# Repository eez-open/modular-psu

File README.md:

### Ownership and License
The contributors are listed in CONTRIB.TXT. 

Licenses | OSHWA UID
--|--
 | 

### Introduction

EEZ Bench Box 3 (BB3) represents a new category of *modular* Test and Measurement (T&M) equipment. It provides a complete open-source hardware and software framework that bridges the gap between – and combines the best features of – DIY hobbyist tools and professional benchtop equipment. 
BB3 was inspired by the [EEZ H24005](https://github.com/eez-open/psu-hw) power supply project ([OSHWA UID HR000001](https://certification.oshwa.org/hr000001.html)), which attracted many enthusiasts with its broad feature-set, rich user interface, DIY-friendliness, and fully open-source design. 
It initially comes with two DC power modules (hence the name of repository *modular-psu*) and will be expanded with new T&M modules (e.g. multi-channel power source, 2/4-quadrant power module, multi-channel temperature sensor module, data logger, switch matrix, digital I/O expander, function generator, data acquisition module, etc.). 
BB3 is made up of the following components:

* _[BP3C](https://github.com/eez-open/modular-psu/tree/master/bp3c)_ EEZ DIB backplane with power output coupling capability of first two modules
* _[AUX power supply](https://github.com/eez-open/modular-psu/tree/master/aux-ps)_ board with AC input protection, soft-start/power-up control, DC fan controller and +5 V / +12 V power outputs
* _[MCU](https://github.com/eez-open/modular-psu/tree/master/mcu)_ board based on STM32F769IIT6 32-bit ARM Cortex-M7
* _[DCP405](https://github.com/eez-open/modular-psu/tree/master/dcp405)_, 0 - 40 V / 50 mA / 5 A DC power source module
* _[DCM224](https://github.com/eez-open/dib-dcm224)_, dual sync buck 1 - 24 V / max. 4.9 A module (**retired**)
* _[Metal enclosure](https://github.com/eez-open/modular-psu/tree/master/enclosure)_ for housing up to 3 modules with 4.3" TFT LCD. Dimensions: 290 (W) x 123 (H) x 240 (D) mm

### Supported technologies

* _EEZ Flow_ (Visual programming tool for test and measurement automation)
* SCPI (Reference Guide in [PDF](https://github.com/eez-open/modular-psu-firmware/blob/master/docs/SCPI%20reference%20guide/EEZ%20BB3%20SCPI%20reference%20guide.pdf))
* MicroPython (script [examples](https://github.com/eez-open/modular-psu-firmware/tree/master/scripts), an example [video](https://www.youtube.com/watch?v=I0y6fgv8G00))
* MQTT (an intro [video](https://www.youtube.com/watch?v=THyfLSSAhrI))
* Node-RED integration (an intro [video](https://www.youtube.com/watch?v=0xQ6Xuq53fA))

### Other DIB modules

* [MIO168](https://github.com/eez-open/dib-mio168) Mixed I/O module
* [PREL6](https://github.com/eez-open/dib-prel6) power relays module
* [SMX46](https://github.com/eez-open/dib-smx46) programmable switch matrix module
* [MUX14D](https://github.com/eez-open/dib-mux14d) dual 7:1 reed relay 2-wire multiplexer

### Related topics and links

* EEZ BB3 [firmware](https://github.com/eez-open/modular-psu-firmware)
* [EEZ Studio](https://www.envox.eu/studio/studio-introduction)
* EEZ [DIB v1.2](https://github.com/eez-open/modular-psu/tree/master/DIB) specification
* EEZ DIB peripheral modules [KiCad 8.x project template](https://github.com/eez-open/dib-kicad-template)
* [Discord](https://discord.gg/dhYMnCB) server
* [X](https://x.com/envox) (ex Twitter)
* [YouTube](https://www.youtube.com/c/eezopen) channel
* [EEVblog forum](https://www.eevblog.com/forum/projects/eez-h25005-a-possible-successor-of-eez-h24005-programmable-power-supply/) discussion
* [Crowd Supply](https://www.crowdsupply.com/envox/eez-bb3) crowdfunding landing page
* [EMC certificate](https://www.envox.eu/?smd_process_download=1&download_id=2806), [LVD cerificate](https://www.envox.eu/?smd_process_download=1&download_id=2808)
* [Sigrok](https://sigrok.org/wiki/Envox_EEZ_Bench_Box_3)
* [Liberpay](https://liberapay.com/eez-open/donate) donations 

### Where to buy?

* [EEZ Web store](https://www.envox.eu/store) (out of stock)
* [Mouser](https://www.mouser.com/Search/Refine?Keyword=cs-bb3-) (kit only, excl. EU/UK)
* [Crowd supply](https://www.crowdsupply.com/envox/eez-bb3) (kit only, excl. EU/UK)

### Security & Regulatory Compliance

* [CRA Compliance Documentation](./security/README.md)

---
Please note that some previous board types and revisions that could be still usable in some cases can be found under *[previous design](https://github.com/eez-open/modular-psu/tree/master/previous%20designs)* folder.

### Notes on Shell Syntax (Community Feedback)
In shell scripting, the syntax used for loops can impact portability and readability across different environments.
Potential Issue with Braces:

 while (( i++ < 10 )) { echo i is $i } 
 
may not work reliably in all shell environments. For instance, in Zsh, this syntax will fail unless SHORT_LOOPS is explicitly enabled.
It can also cause issues with syntax highlighting and script execution.

* Alternate Approach: To ensure broader compatibility and clearer syntax, prefer the standard do ... done block structure:

i=0
while (( i++ < 10 ))
do
 echo "i is $i"
done

This format is - Compatible with most POSIX-compliant shells (e.g., Bash, Zsh, etc.) and Syntax-highlight friendly in editors and IDEs.

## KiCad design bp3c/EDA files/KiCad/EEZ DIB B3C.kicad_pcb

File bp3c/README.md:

EEZ DIB BP3C is backplane for connecting up to three EEZ DIB peripheral modules. When power modules (e.g. [DCP405](https://github.com/eez-open/modular-psu/tree/master/dcp405)) are plugged into slot #1 and #2, their outputs can be combined under firmware control in one of the following way:

- Serial coupling to double max. output voltage 
- Parallel coupling to double max. output current
- Ch#1 `Out-` and Ch#2 `Out+` coupling for split rail output

Additionaly, it is possible to couple `Out-` terminals of all installed power modules (common GND).

The BP3C backplane provides dedicated BOOT output for each peripheral module that comes with on-board MCU and which firmware could be uploaded via SPI or UART. Programmable reset output is also featured that firmware upload procedure can be initiated without power recycling.

Dimensions: 110 x 90 mm, 2-layer PCB

### KiCad project (v7 or newer)

* [BP3C r3B3](https://github.com/eez-open/modular-psu/tree/master/bp3c/EDA%20files/KiCad)

All symbols, footprints and 3D models used in the project can be found in the [EEZ-DIB Library](https://github.com/eez-open/eez-kicad-libraries) plugin for KiCad.

### Bill of materials

* [Download](https://github.com/eez-open/modular-psu/blob/master/bp3c/EDA%20files/KiCad/bom/ibom.html) as raw file _Interactive BOM_ (ibom.html) and open it locally in your browser.

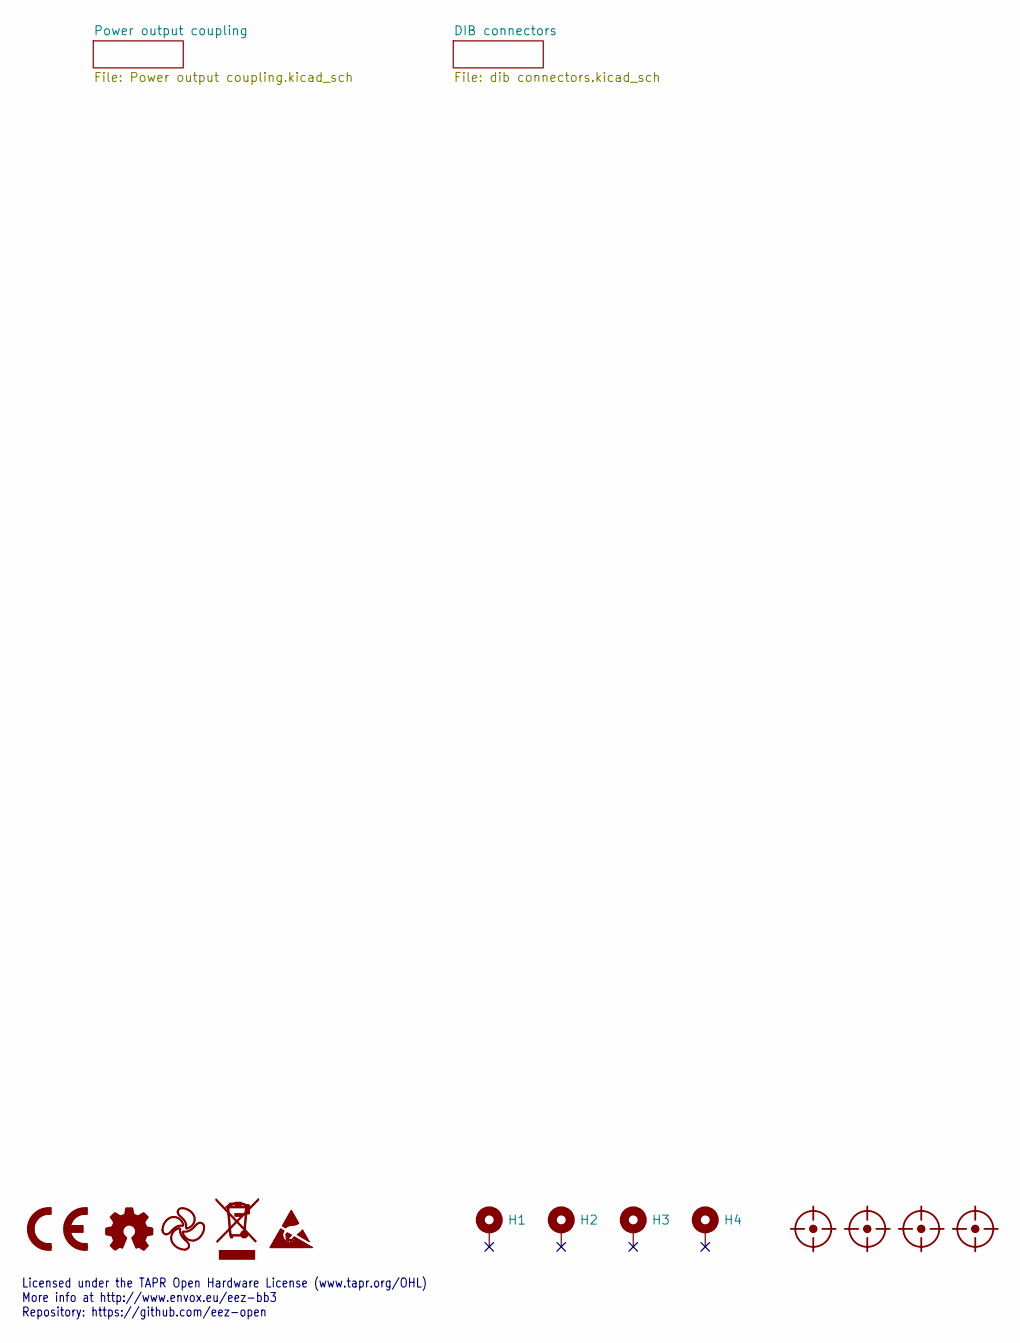
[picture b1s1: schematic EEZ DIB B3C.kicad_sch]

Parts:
FM1, FM2, FM3, FM4: FIDUCIAL; Fiducial
H1, H2, H3, H4: Mounting_hole 3.2_5.5mm
LOGO1: CR logo; CE logo
LOGO2: Open HW logo
LOGO3: EEZ logo; EEZ logo (outline 6mm)
LOGO4: WEEE logo
LOGO5: ESD logo

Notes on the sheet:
Licensed under the TAPR Open Hardware License (www.tapr.org/OHL) More info at http://www.envox.eu/eez-bb3 Repository: https://github.com/eez-open

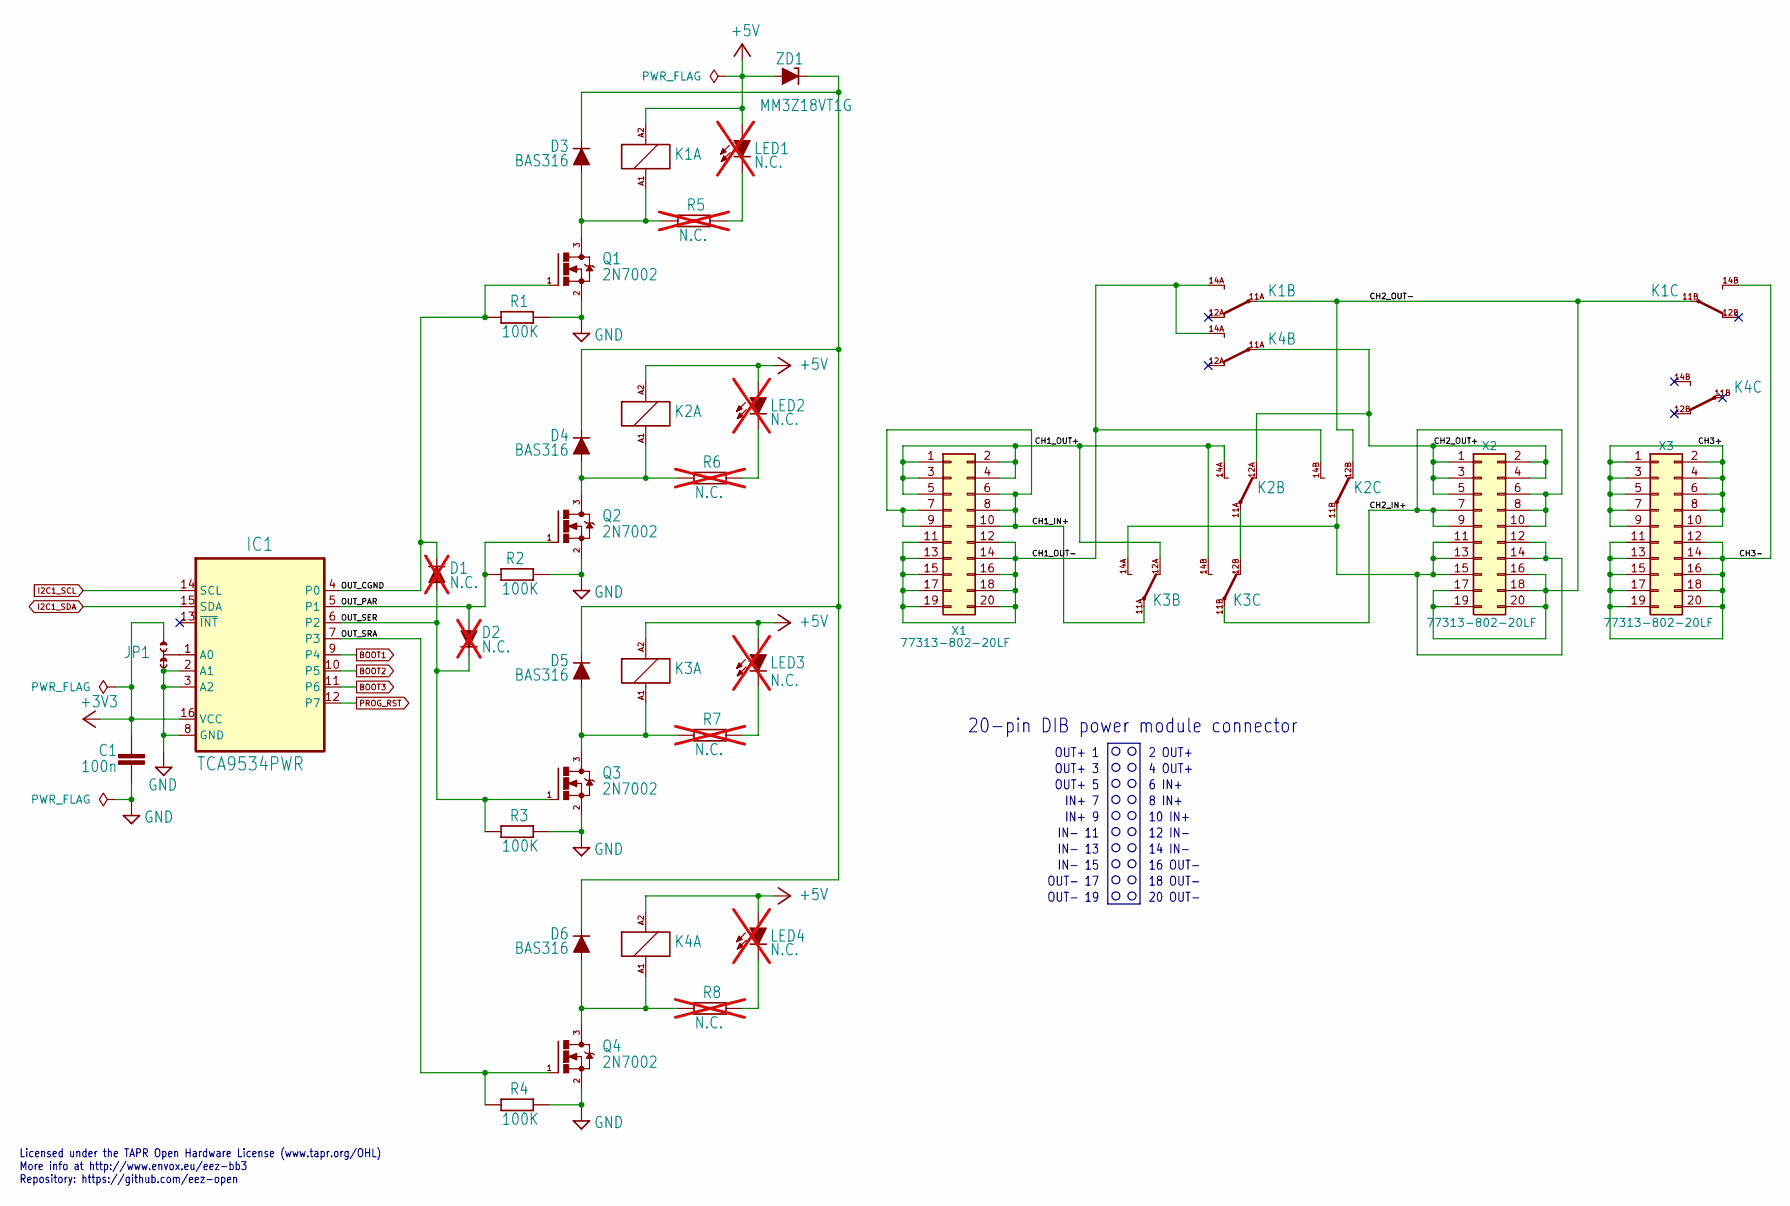
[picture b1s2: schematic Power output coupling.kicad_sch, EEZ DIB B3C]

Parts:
C1: 100n; C_0603_1608Metric; DigiKey 1276-1005-2-ND
D1, D2: N.C.; SOD-323_1P8X1P35_ONS-M; not fitted
D3, D4, D5, D6: BAS316; SOD-323_1P8X1P35_ONS-M; DigiKey 1727-7370-1-ND
IC1: TCA9534PWR; PW(R-PDSO-G16); DigiKey 296-40574-1-ND
JP1: JP3-CUT; JP3 shorted
K1, K2, K3, K4: RT424005; DigiKey PB1998-ND
LED1, LED2, LED3, LED4: N.C.; LED_LTST-C170KGKT_LTO-L; DigiKey 160-1414-2-ND; not fitted
Q1, Q2, Q3, Q4: 2N7002; SOT103P240X110-3N; DigiKey T2N7002AKLMCT-ND
R1, R2, R3, R4: 100K; R_0805_2012Metric; DigiKey RMCF0805FT100KCT-ND
R5, R6, R7, R8: N.C.; R_0805_2012Metric; not fitted
X1, X2, X3: 77313-802-20LF; DigiKey 609-77313-802-20LF-ND
ZD1: MM3Z18VT1G; SOD-323_1P8X1P35_ONS-M; DigiKey MM3Z18VT1GOSCT-ND

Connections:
+3V3: C1.1, IC1.16 (VCC), JP1.NO; also elsewhere on the board
+5V: K1.A2 (C1), K2.A2 (C1), K3.A2 (C1), K4.A2 (C1), LED1.A, LED2.A, LED3.A, LED4.A, ZD1.A; also elsewhere on the board
/Power output coupling/CH1_IN+: K3.11A, X1.6, X1.7, X1.8, X1.9, X1.10
/Power output coupling/CH1_OUT+: K2.14A (O), K3.12A (S), K3.14B (O), X1.1, X1.2, X1.3, X1.4, X1.5
/Power output coupling/CH1_OUT-: K1.14A (O), K2.14B (O), K4.14A (O), X1.11, X1.12, X1.13, X1.14, X1.15, X1.16, X1.17, X1.18, X1.19, X1.20
/Power output coupling/CH2_IN+: K3.11B, X2.6, X2.7, X2.8, X2.9, X2.10
/Power output coupling/CH2_OUT+: K2.12A (S), K4.11A, X2.1, X2.2, X2.3, X2.4, X2.5
/Power output coupling/CH2_OUT-: K1.11A, K1.11B, K2.12B (S), X2.16, X2.17, X2.18, X2.19, X2.20
/Power output coupling/CH3+: X3.1, X3.2, X3.3, X3.4, X3.5, X3.6, X3.7, X3.8, X3.9, X3.10
/Power output coupling/CH3-: K1.14B (O), X3.11, X3.12, X3.13, X3.14, X3.15, X3.16, X3.17, X3.18, X3.19, X3.20
/Power output coupling/OUT_CGND: D1.C, IC1.4 (P0), Q1.1 (G), R1.2
/Power output coupling/OUT_PAR: D2.A, IC1.5 (P1), Q2.1 (G), R2.2
/Power output coupling/OUT_SER: D1.A, D2.C, IC1.6 (P2), Q3.1 (G), R3.2
/Power output coupling/OUT_SRA: IC1.7 (P3), Q4.1 (G), R4.2
BOOT1: IC1.9 (P4); also elsewhere on the board
BOOT2: IC1.10 (P5); also elsewhere on the board
BOOT3: IC1.11 (P6); also elsewhere on the board
GND: C1.2, IC1.2 (A1), IC1.3 (A2), IC1.8 (GND), JP1.NC, Q1.2 (S), Q2.2 (S), Q3.2 (S), Q4.2 (S), R1.1, R2.1, R3.1, R4.1; also elsewhere on the board
I2C1_SCL: IC1.14 (SCL); also elsewhere on the board
I2C1_SDA: IC1.15 (SDA); also elsewhere on the board
unnamed: D3.C, D4.C, D5.C, D6.C, ZD1.C
unnamed: IC1.1 (A0), JP1.COM
unnamed: D3.A, K1.A1 (C2), Q1.3 (D), R5.2
unnamed: D4.A, K2.A1 (C2), Q2.3 (D), R6.2
unnamed: K2.11A, K3.12B (S)
unnamed: K2.11B, K3.14A (O), X2.11, X2.12, X2.13, X2.14, X2.15
unnamed: D5.A, K3.A1 (C2), Q3.3 (D), R7.2
unnamed: D6.A, K4.A1 (C2), Q4.3 (D), R8.2
unnamed: LED1.C, R5.1
unnamed: LED2.C, R6.1
unnamed: LED3.C, R7.1
unnamed: LED4.C, R8.1
PROG_RST: IC1.12 (P7); also elsewhere on the board

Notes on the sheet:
14 IN-
Licensed under the TAPR Open Hardware License (www.tapr.org/OHL) More info at http://www.envox.eu/eez-bb3 Repository: https://github.com/eez-open
OUT+ 5
6 IN+
12 IN-
IN- 15
IN- 13
IN+ 9
IN+ 7
IN- 11
16 OUT-
20-pin DIB power module connector
OUT- 17
OUT- 19
10 IN+
OUT+ 3
18 OUT-
OUT+ 1
2 OUT+
4 OUT+
8 IN+
20 OUT-

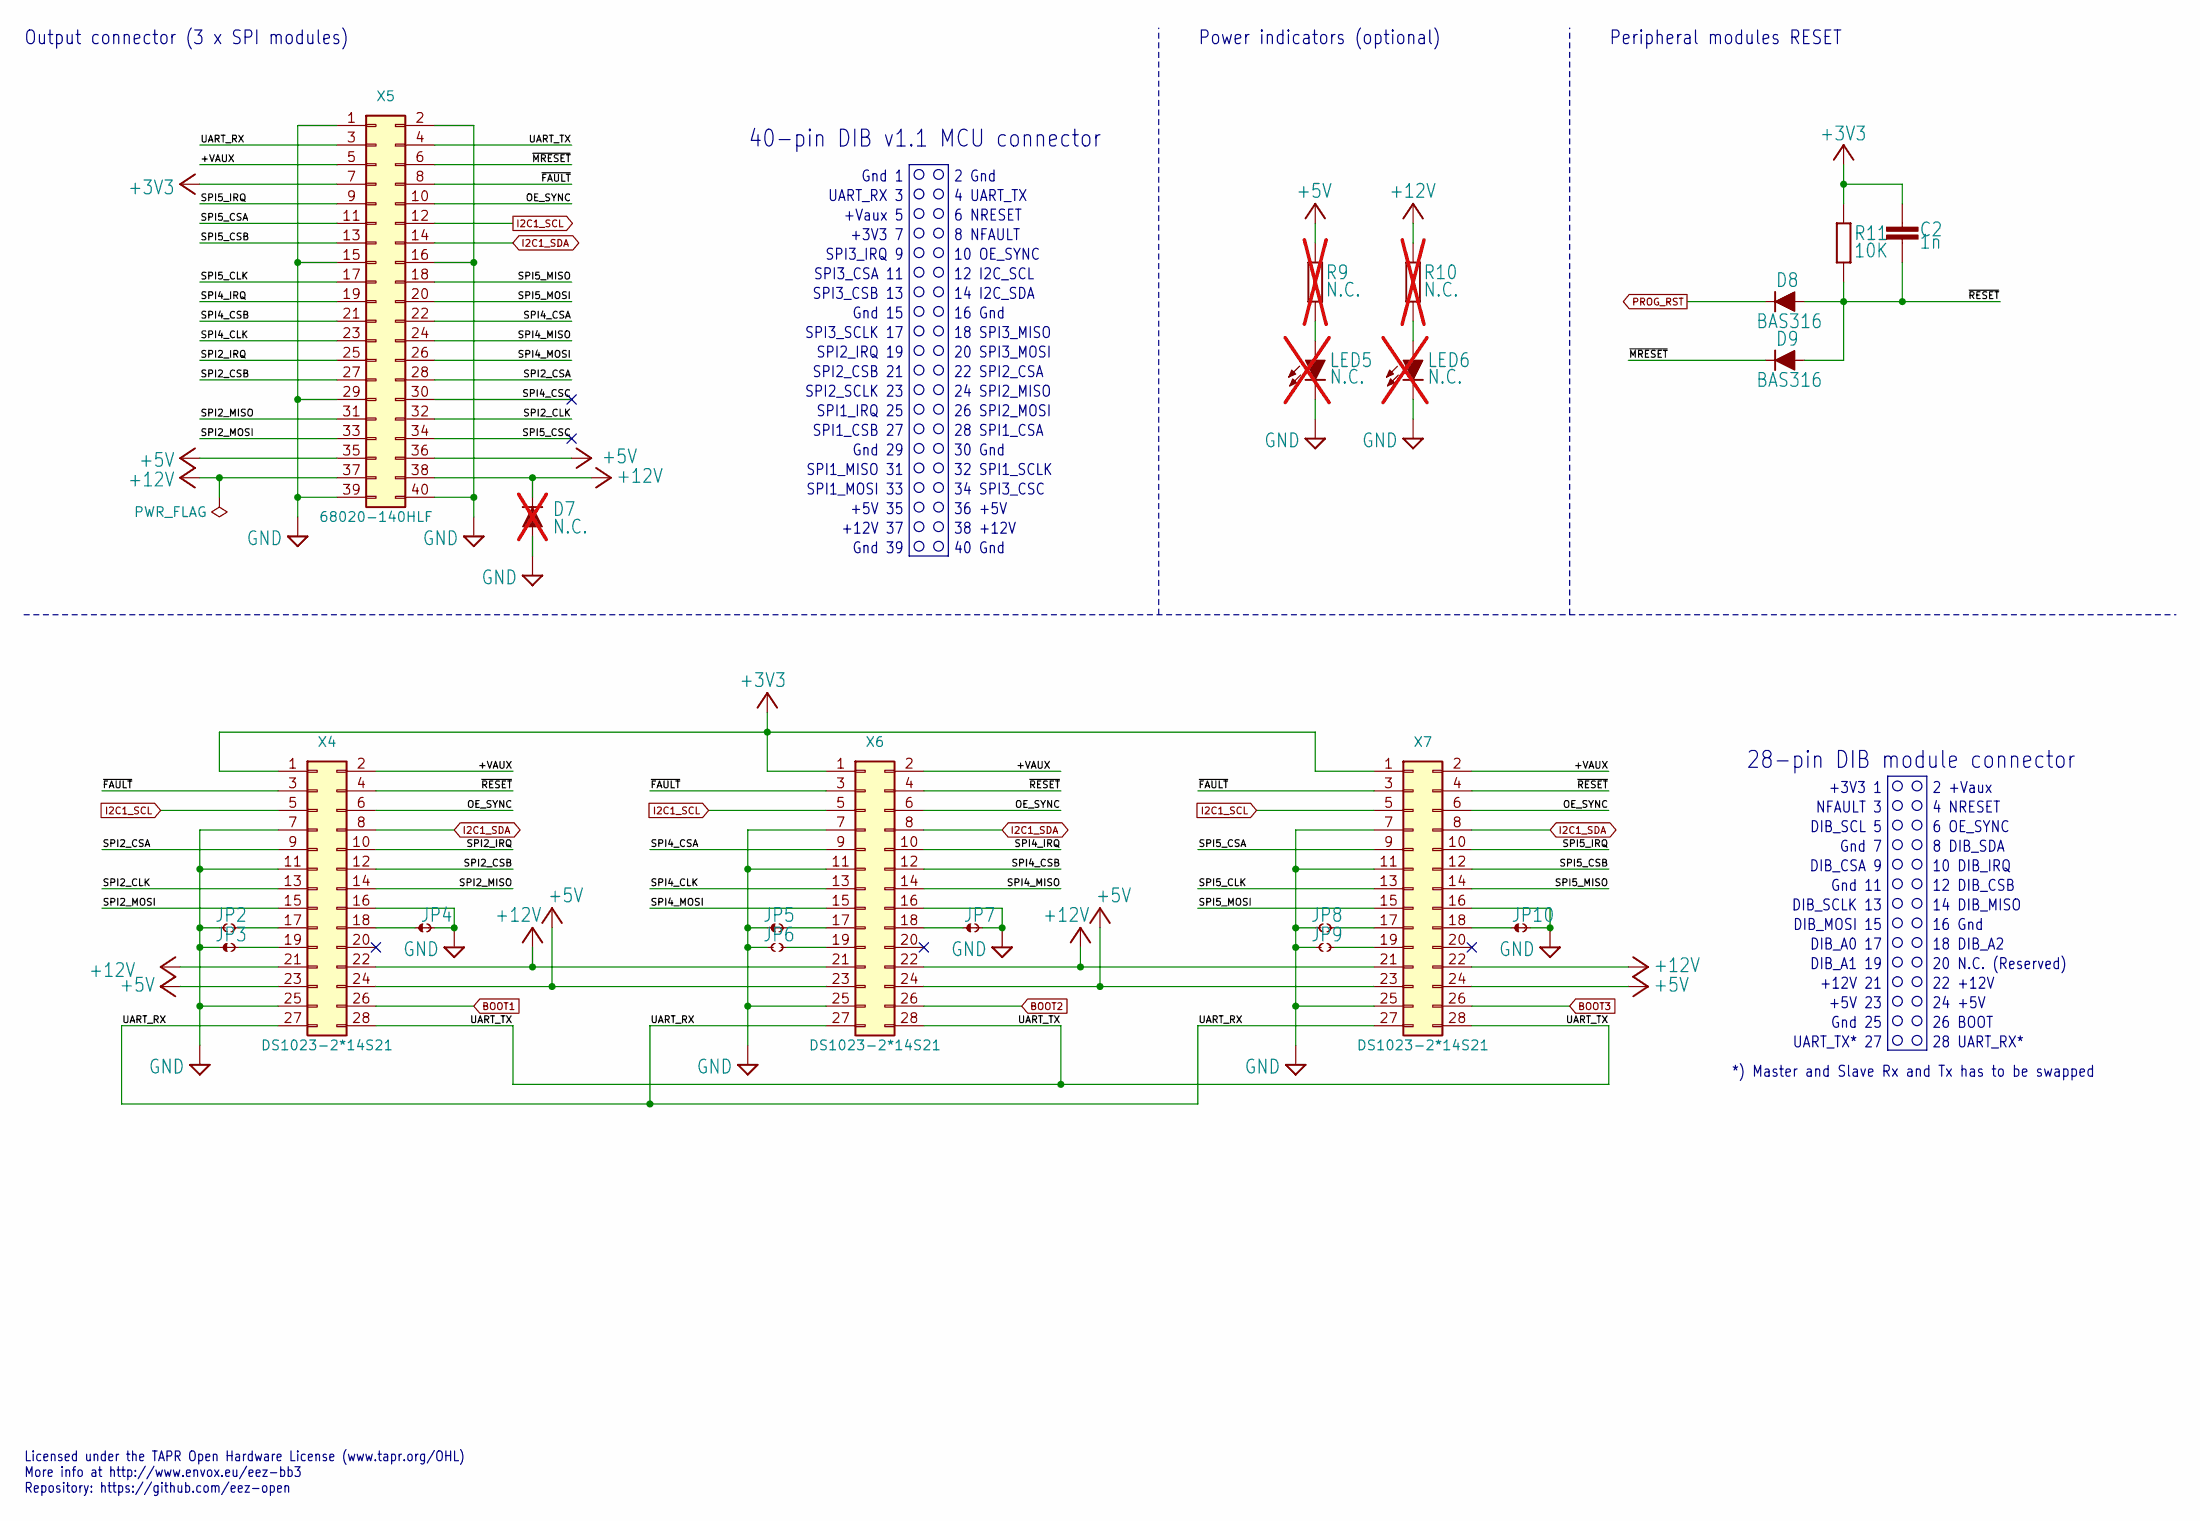
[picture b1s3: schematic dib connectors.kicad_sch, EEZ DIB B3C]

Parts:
C2: 1n; C_0805_2012Metric; DigiKey 732-7858-1-ND
D7: N.C.; DO214AA; not fitted
D8, D9: BAS316; SOD-323_1P8X1P35_ONS-M; DigiKey 1727-7370-1-ND
JP2, JP6, JP8, JP9: JP2-CUT; JP2 open
JP3, JP4, JP5, JP7, JP10: JP2-NOCUT; JP2 shorted
LED5, LED6: N.C.; LED_LTST-C170KGKT_LTO-L; DigiKey 160-1414-2-ND; not fitted
R9, R10: N.C.; R_0805_2012Metric; not fitted
R11: 10K; R_0805_2012Metric; DigiKey 311-10.0KCRCT-ND
X4, X6, X7: DS1023-2*14S21; TSW-114-07-F-D; DigiKey S7082-ND
X5: 68020-140HLF; DigiKey 68020-140HLF-ND

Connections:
+3V3: C2.2, R11.1, X4.1, X5.7, X6.1, X7.1; also elsewhere on the board
+5V: R9.1, X4.23, X4.24, X5.35, X5.36, X6.23, X6.24, X7.23, X7.24; also elsewhere on the board
+12V: D7.C, R10.1, X4.21, X4.22, X5.37, X5.38, X6.21, X6.22, X7.21, X7.22
/DIB connectors/+VAUX: X4.2, X5.5, X6.2, X7.2
/DIB connectors/OE_SYNC: X4.6, X5.10, X6.6, X7.6
/DIB connectors/SPI2_CLK: X4.13, X5.32
/DIB connectors/SPI2_CSA: X4.9, X5.28
/DIB connectors/SPI2_CSB: X4.12, X5.27
/DIB connectors/SPI2_IRQ: X4.10, X5.25
/DIB connectors/SPI2_MISO: X4.14, X5.31
/DIB connectors/SPI2_MOSI: X4.15, X5.33
/DIB connectors/SPI4_CLK: X5.23, X6.13
/DIB connectors/SPI4_CSA: X5.22, X6.9
/DIB connectors/SPI4_CSB: X5.21, X6.12
/DIB connectors/SPI4_CSC: X5.30
/DIB connectors/SPI4_IRQ: X5.19, X6.10
/DIB connectors/SPI4_MISO: X5.24, X6.14
/DIB connectors/SPI4_MOSI: X5.26, X6.15
/DIB connectors/SPI5_CLK: X5.17, X7.13
/DIB connectors/SPI5_CSA: X5.11, X7.9
/DIB connectors/SPI5_CSB: X5.13, X7.12
/DIB connectors/SPI5_CSC: X5.34
/DIB connectors/SPI5_IRQ: X5.9, X7.10
/DIB connectors/SPI5_MISO: X5.18, X7.14
/DIB connectors/SPI5_MOSI: X5.20, X7.15
/DIB connectors/UART_RX: X4.27, X5.3, X6.27, X7.27
/DIB connectors/UART_TX: X4.28, X5.4, X6.28, X7.28
/DIB connectors/~FAULT: X4.3, X5.8, X6.3, X7.3
/DIB connectors/~MRESET: D9.C, X5.6
/DIB connectors/~RESET: C2.1, D8.A, D9.A, R11.2, X4.4, X6.4, X7.4
BOOT1: X4.26; also elsewhere on the board
BOOT2: X6.26; also elsewhere on the board
BOOT3: X7.26; also elsewhere on the board
GND: D7.A, JP2.1, JP3.1, JP4.2, JP5.1, JP6.1, JP7.2, JP8.1, JP9.1, JP10.2, LED5.C, LED6.C, X4.7, X4.11, X4.16, X4.25, X5.1, X5.2, X5.15, X5.16, X5.29, X5.39, X5.40, X6.7, X6.11, X6.16, X6.25, X7.7, X7.11, X7.16, X7.25; also elsewhere on the board
I2C1_SCL: X4.5, X5.12, X6.5, X7.5; also elsewhere on the board
I2C1_SDA: X4.8, X5.14, X6.8, X7.8; also elsewhere on the board
unnamed: LED5.A, R9.2
unnamed: LED6.A, R10.2
unnamed: JP2.2, X4.17
unnamed: JP4.1, X4.18
unnamed: JP3.2, X4.19
unnamed: JP5.2, X6.17
unnamed: JP7.1, X6.18
unnamed: JP6.2, X6.19
unnamed: JP8.2, X7.17
unnamed: JP10.1, X7.18
unnamed: JP9.2, X7.19
PROG_RST: D8.C; also elsewhere on the board

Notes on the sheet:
Gnd 11
SPI2_SCLK 23
8 NFAULT
Gnd 25
UART_TX* 27
4 NRESET
Peripheral modules RESET
26 BOOT
18 SPI3_MISO
24 +5V
6 NRESET
SPI1_CSB 27
28 UART_RX*
28 SPI1_CSA
38 +12V
22 SPI2_CSA
Gnd 15
Output connector (3 x SPI modules)
SPI1_IRQ 25
DIB_SCLK 13
8 DIB_SDA
Gnd 1
+5V 23
40-pin DIB v1.1 MCU connector
+12V 37
DIB_SCL 5
SPI2_IRQ 19
14 DIB_MISO
2 Gnd
+5V 35
18 DIB_A2
12 I2C_SCL
2 +Vaux
SPI3_CSB 13
10 DIB_IRQ
16 Gnd
SPI1_MOSI 33
DIB_MOSI 15
*) Master and Slave Rx and Tx has to be swapped
SPI3_CSA 11

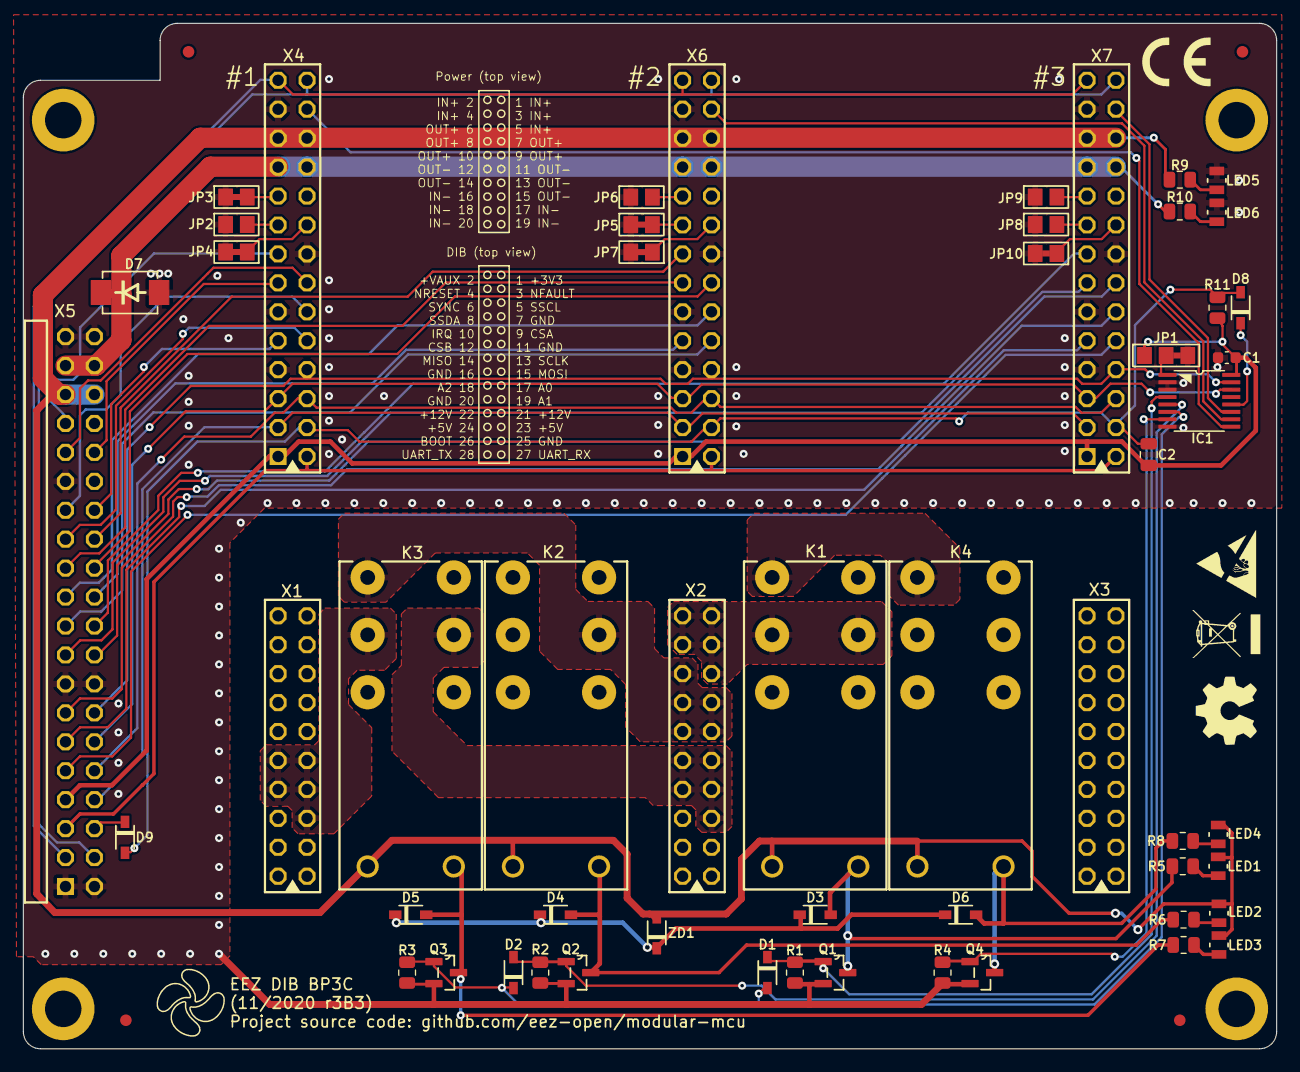
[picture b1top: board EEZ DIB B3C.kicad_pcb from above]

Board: 2 copper layers, 110.0 x 90.0 mm, 68 parts (0 on the bottom side), 70 nets.

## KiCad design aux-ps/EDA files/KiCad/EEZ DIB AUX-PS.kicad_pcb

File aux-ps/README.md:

### Overview

_IMPORTANT: A crowdfunded version of the AUX-PS (r3B3) can be found [here](https://github.com/eez-open/modular-psu/tree/master/previous%20designs/aux-ps%20r3B3%20(Crowd%20Supply%20edition))._

AUX Power supply board for powering MCU board and backplane. It includes fan controller and AC power control with softstart (inrush current limiter) for power modules like DCP405 and DCM224.

### Feature list

* On-board IEC C14 AC inlet with dual 20 x 5 mm fuses
* On-board AC power switch
* AC input protection (SAR, MOV)
* AC input filter for EMI compliance
* 3 x AC power outputs
* Soft-start/standby relay control
* +5 V, 10 W (optional 20 W)
* +12 V, 10 W
* I2C DC fan controller with temperature sensor and speed control
* Two 3-wire or 4-wire 12V DC fans (standard PC fan pinout)
* Standby LED indictor
* On-board PE 4 mm terminal
* AC mains frequency detection (optional)
* Dimensions: 230.5 x 60 mm, 2-layer PCB
* **CE certified design**

### KiCad project (v7 or newer)

* [AUX-PS r3B7](https://github.com/eez-open/modular-psu/tree/master/aux-ps/EDA%20files/KiCad)

All symbols, footprints and 3D models used in the project can be found in the [EEZ-DIB Library](https://github.com/eez-open/eez-kicad-libraries) plugin for KiCad.

### Bill of materials

* [Download](https://github.com/eez-open/modular-psu/blob/master/aux-ps/EDA%20files/KiCad/bom/ibom.html) as raw file _Interactive BOM_ (ibom.html) and open it locally in your browser.

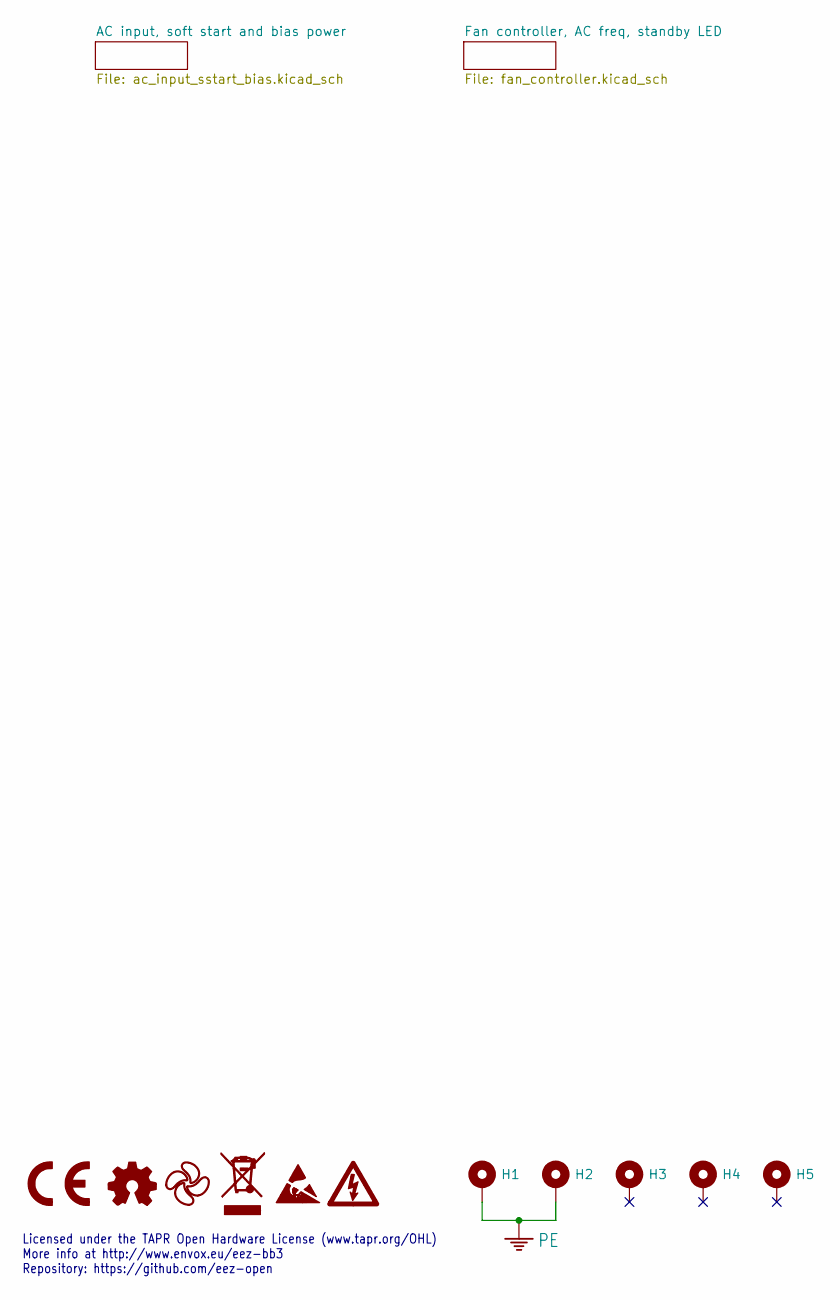
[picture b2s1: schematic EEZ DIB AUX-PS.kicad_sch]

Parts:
H1, H2, H3, H4, H5: Mounting_hole 3.2_5.5mm
LOGO1: CR logo; CE logo
LOGO2: Open HW logo
LOGO3: EEZ logo; EEZ logo (outline 6mm)
LOGO4: WEEE logo
LOGO5: ESD logo
LOGO6: Hi voltage logo

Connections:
PE: H1.1, H2.1; also elsewhere on the board

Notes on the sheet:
Licensed under the TAPR Open Hardware License (www.tapr.org/OHL) More info at http://www.envox.eu/eez-bb3 Repository: https://github.com/eez-open

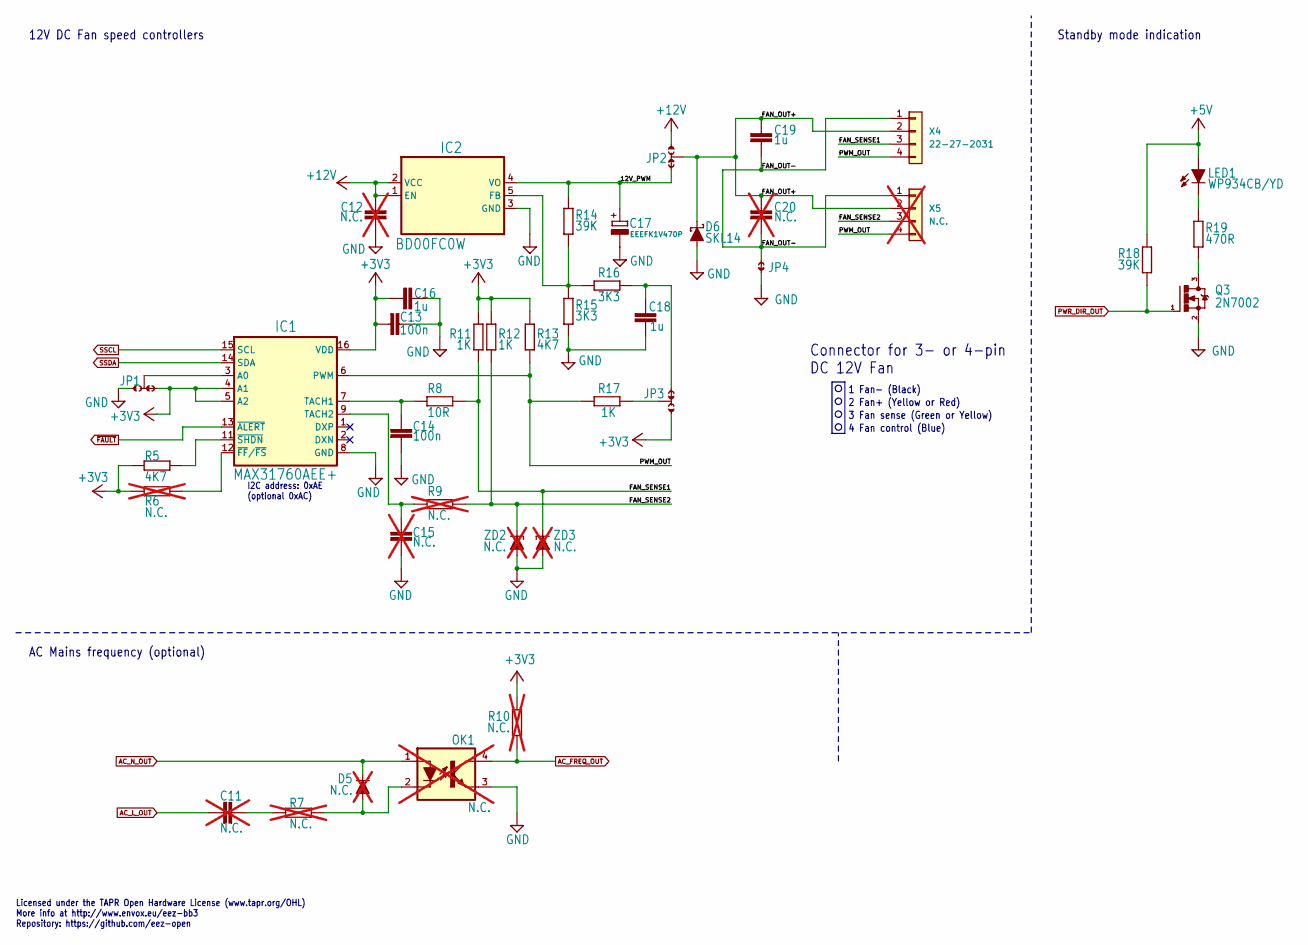
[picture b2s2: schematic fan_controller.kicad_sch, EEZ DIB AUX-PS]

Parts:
C11: N.C.; C102-054X133; not fitted
C12, C20: N.C.; C_0805_2012Metric; not fitted
C13, C14: 100n; C_0603_1608Metric; DigiKey 1276-1005-2-ND
C15: N.C.; C_0603_1608Metric; not fitted
C16, C18, C19: 1u; C_0805_2012Metric; DigiKey 490-10494-2-ND
C17: EEEFK1V470P; CAPAE660X610N; DigiKey PCE3842CT-ND
D5: N.C.; SOD-323_1P8X1P35_ONS-M; not fitted
D6: SKL14; SOD123; DigiKey 1727-7335-1-ND
IC1: MAX31760AEE+; DBQ16; DigiKey MAX31760AEE+-ND
IC2: BD00FC0W; TO-252-5; DigiKey BD00FC0WFP-E2TR-ND
JP1, JP2, JP3: JP3-CUT-0805-ROTATED; JP3 shorted
JP4: JP2-NOCUT-0805; JP2 shorted
LED1: WP934CB/YD; WP934CB_YD; DigiKey 754-1300-ND
OK1: N.C.; SOIC127P700X210-4N; DigiKey TLP291(GBSE-ND; not fitted
Q3: 2N7002; SOT103P240X110-3N; DigiKey T2N7002AKLMCT-ND
R5, R13: 4K7; R_0805_2012Metric; DigiKey 311-4.70KCRCT-ND
R6, R7, R9, R10: N.C.; R_0805_2012Metric; not fitted
R8: 10R; R_0805_2012Metric; DigiKey 311-10.0CRTR-ND
R11, R12, R17: 1K; R_0805_2012Metric; DigiKey 311-1.00KCRTR-ND
R14, R18: 39K; R_0805_2012Metric; DigiKey RMCF0805FT39K0CT-ND
R15, R16: 3K3; R_0805_2012Metric; DigiKey A129755CT-ND
R19: 470R; R_0805_2012Metric; DigiKey 311-470CRCT-ND
X4: 22-27-2031; 22-27-2041 (3-pin only); DigiKey WM4112-ND
X5: N.C.; 22-27-2041 (3-pin only); not fitted
ZD2, ZD3: N.C.; SOD123; not fitted

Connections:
+3V3: C13.2, C16.2, IC1.4 (A1), IC1.5 (A2), IC1.16 (VDD), JP1.NC, JP3.NO, R5.2, R6.2, R10.1, R11.2, R12.2, R13.2; also elsewhere on the board
+5V: LED1.A, R18.1; also elsewhere on the board
+12V: C12.1, IC2.1 (EN), IC2.2 (VCC), JP2.NO; also elsewhere on the board
/Fan controller, AC freq, standby LED/12V_PWM: C17.+, IC2.4 (VO), JP2.NC, R14.1
/Fan controller, AC freq, standby LED/FAN_OUT+: C19.1, C20.1, D6.C, JP2.COM, X4.2, X5.2
/Fan controller, AC freq, standby LED/FAN_OUT-: C19.2, C20.2, JP4.2, X4.1, X5.1
/Fan controller, AC freq, standby LED/FAN_SENSE1: R8.2, R11.1, X4.3, ZD3.C
/Fan controller, AC freq, standby LED/FAN_SENSE2: R9.2, R12.1, X5.3, ZD2.C
/Fan controller, AC freq, standby LED/PWM_OUT: IC1.6 (PWM), R13.1, R17.2, X4.4, X5.4
AC_FREQ_OUT: OK1.4 (COL), R10.2; also elsewhere on the board
AC_L_OUT: C11.1; also elsewhere on the board
AC_N_OUT: D5.C, OK1.1 (A); also elsewhere on the board
GND: C12.2, C13.1, C14.2, C15.2, C16.1, C17.-, C18.2, D6.A, IC1.8 (GND), IC2.3 (GND), JP1.NO, JP4.1, OK1.3 (EMIT), Q3.2 (S), R15.2, ZD2.A, ZD3.A; also elsewhere on the board
unnamed: C11.2, R7.1
unnamed: C18.1, JP3.NC, R16.2
unnamed: IC1.3 (A0), JP1.COM
unnamed: C14.1, IC1.7 (TACH1), R8.1
unnamed: C15.1, IC1.9 (TACH2), R9.1
unnamed: IC1.12 (~FF/~FS), R6.1
unnamed: IC1.11 (~SHDN), R5.1
unnamed: IC2.5 (FB), R14.2, R15.1, R16.1
unnamed: JP3.COM, R17.1
unnamed: LED1.C, R19.1
unnamed: D5.A, OK1.2 (C), R7.2
unnamed: Q3.3 (D), R19.2
PWR_DIR_OUT: Q3.1 (G), R18.2; also elsewhere on the board
SSCL: IC1.15 (SCL); also elsewhere on the board
SSDA: IC1.14 (SDA); also elsewhere on the board
~FAULT: IC1.13 (~ALERT); also elsewhere on the board

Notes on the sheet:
12V DC Fan speed controllers
AC Mains frequency (optional)
Standby mode indication
1 Fan- (Black)
4 Fan control (Blue)
3 Fan sense (Green or Yellow)
I2C address: 0xAE (optional 0xAC)
Connector for 3- or 4-pin DC 12V Fan
Licensed under the TAPR Open Hardware License (www.tapr.org/OHL) More info at http://www.envox.eu/eez-bb3 Repository: https://github.com/eez-open
2 Fan+ (Yellow or Red)

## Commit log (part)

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2018-08-29 Fixed Airwire in Eagle
    Fixed some existing Airwires in de Eagle Board
2018-08-29 Fixed Wire Stubs
    Fixed some Wire Stubs in the Eagle Design
2018-08-29 Converted Eagle Project to KiCad
    I importet the Eagle files to KiCad, so everybody can join and work on the pcb design with free open source software.
2018-08-29 Rename of the sheets
    Fixed the nameing of the sheets from the import into KiCad
2018-09-06 first version of AUX PS board
2018-09-07 mcu board BOM
2018-09-07 aux-ps BOM update, PE terminals added
2018-09-08 minor changes in BOMs
2018-09-08 changed AC capacitors to X2 class
2018-09-08 Kicad-ised schematic, fixed import errors
    Basic stuff like pin functions not assigned, and moving to heirarchial labels instead of global,
2018-09-08 Generated Netlist
    The netlist allows verification between SCH and PCB in kicad, so important for any newcomers who may try and use it.
2018-09-08 Generated Netlist File
    The netlist is an important file for linking SCH and PCB in kicad, it should be included to make it easy for newcomers,
2018-09-08 PCB Trace Matching to RAM
2018-09-09 Updating Kicad Files to r1B2
    Some component Values and connections had changed since r1B1 when kicad file was last converted, brought sch and pcb up to current eagle file.
2018-09-09 Left PE Ground trace dangling on USB connector
    Connected PE Trace, and 5V to L1,
2018-09-09 Refill Zones...
2018-09-12 mcu board prototype picture
2018-09-12 aux-ps SW1 adjustment
2018-09-14 SW2 changed
2018-09-14 mcu board C3 relocated
2018-09-15 Updating Kicad Files To Reflect Latest Commits
2018-09-25 .ioc changes for TFT, USB and SDRAM
2018-09-26 .ioc changes for ETH (25 MHz master clock)
2018-10-05 r1B2 changes
2018-10-06 PS AUX updated values for R30, C23
2018-10-06 PS AUX parts image updated
2018-10-18 MCU fixes: #10, #13, #15, #16, #17, #18
2018-11-05 #23, #24
2018-12-14 readme.md update
2018-12-30 first commit of DCP505 power board
2018-12-30 readme.md link fix
2018-12-30 small fixes
2018-12-31 PCB inductor added in schematics
2018-12-31 small PCB optimizations
2019-01-01 first bp3c commit
2019-01-02 SW1 position adjustment
2019-01-02 BP3C module addressing fix
2019-01-03 MCU JP4 added
2019-01-03 DCP505: replaced temperature sensor (IC7)
2019-01-03 fix PCB inductor dimensions
2019-01-03 removed hole on THT MOSFETs packages
2019-01-07 parts values and types corrections
2019-01-21 #26, #28, #29
2019-01-23 DCP505 fault indication fix
2019-01-24 MCU board minor changes
2019-01-24 AUX PS C2 moved away on the PCB from X1
2019-01-26 board pictures updated
2019-01-27 .ioc file for MCU r1B2
2019-02-02 enclosure fan holes corrected
2019-02-02 enclosure silkscreens
2019-02-02 module panel template
2019-02-07 #30, #31, #32
2019-02-07 enclosure holes fix for AUX PS
2019-02-07 pullup on fan controller SHDN pin, enclosure silkscreens updated
2019-03-09 temp. sensor C9 added
2019-03-16 X3 changed to vertical
2019-03-27 PE to Gnd caps added
2019-04-14 DCP405 module first commit
2019-04-14 chassis silkscreens adjustments
2019-04-24 DCP405 BOM
2019-05-19 DCP405 BOM update, JP2 added
2019-05-19 DCP405 JP3, JP4 added
2019-05-27 improved routing related to #40
2019-06-02 BP3C minor fixes
2019-06-08 add buydisplay.com TFT into MCU BOM
2019-06-08 #37, jumper replaced with micro switch
2019-06-08 #37, micro switch moved left
2019-06-14 MCU board chages for #37, #42
2019-06-14 MCU board Vdd trace fixed
2019-06-16 #37, place for optional jumper added
2019-06-18 major reorganization, introduced new PS AUX and BP3C that covers #37, #41
2019-06-18 readme.md links fixed
2019-06-18 enclosure front panel and DCP405 heatsink changes
2019-06-19 first prototype picture added
2019-06-19 enclosure dimensions corrected in readme.md
2019-06-19 BP3C module connectors moved up 0.5mm
2019-06-26 readme.md fix
2019-06-26 DCM220 sch update
2019-06-29 #44, #45
2019-06-29 DCM220, C36 value update
2019-06-29 #44, #45 Eagle files
2019-07-01 MCU board BOM update
2019-07-01 AUX PS BOM update
2019-07-01 BP3C readme.md update
2019-07-02 MCU J1 update
2019-07-02 MCU optional I/O protection
2019-07-04 DCM220 R8 value fixed
2019-07-10 enclosure prototype image update
2019-07-10 TVS added on outputs
2019-07-10 MCU Gerbers update
2019-07-13 update TME connectors in BOMs
2019-07-13 AUX-PS PCB redesign
2019-07-13 AUX-PS readme.md update
2019-07-13 BP3C BOM update
2019-07-16 PCB test tabs added
2019-07-21 DCP405 r2B5
2019-07-21 DCM220 name on PCB fixed
2019-07-23 multiple BOMs update
2019-07-24 enlosure BOM update
2019-07-24 multiple PCB layout adjustments
2019-07-24 micro SD card added into MCU BOM
2019-07-24 display support drawings added
2019-08-02 DCP405 BOM update
2019-08-04 MCU BOM update
2019-08-08 enclosure rear panel update
2019-08-08 enclosure BOM update
2019-08-09 Fan LDO control fixed
2019-08-15 DCP405 r2B6 (w/o BOM)
2019-08-17 DCM220 front panel corrections
2019-08-26 DCP405 r2B6 BOM
2019-08-28 AUX PS PWM pullup added
2019-08-28 MCU user sw cap changed to white
2019-08-28 MCU r1B5 STM32 .ioc
2019-08-29 pullup on enc sw in .ioc
2019-08-30 DCP405 CC comp correction
2019-08-30 DCP405 reverse sense clean up
2019-09-03 MCU reset issue, encoder moved
2019-09-04 DCP405 BOM and front panel update
2019-09-04 DCM220 r2B2 .ioc file
2019-09-06 AUX-PS softstart pull-downs changed
2019-09-11 DCP405 readme.md update
2019-09-18 BP3C reset fix
2019-09-18 #48, replaced DAC with PWM
2019-09-18 module front panels update
2019-09-18 AUX-PS SW2 replaced with tactile switch
2019-09-19 prereg Rsense to R008
2019-09-21 DCM220 I_SET gain adjustment
2019-09-21 DCP405 CV, CC compensations adjustment
2019-09-21 MCU IC2 label added
2019-09-26 DCP405 OVP up-programming adjustment
2019-09-26 DCP405 OVP U_SET fixed
2019-10-02 BOM updates
2019-10-03 DCM220 IC2 bottom stop mask correction
2019-10-06 DCM220 r2B4
2019-10-06 DCP405 Q18 added to HW OVP
2019-10-08 DCM220 diff. opamps gain correction
2019-10-08 DCM220 eagle files
2019-10-11 DCM220 r2B4 .ioc update
2019-10-12 Enclosure BOM update (M3x8 countersink for AC inlet)
2019-10-12 Enclosure and AUX-PS BOM updates
2019-10-16 new enclosure picture
2019-10-27 DCM220 r2B5
2019-10-28 DCP405 OE slow down
2019-10-28 new AC/DC power modules mounting plate
2019-10-31 DCM220 PCB corrections
2019-11-06 BOMs update
2019-11-18 front panel Tx/Rx swap, BOM updates
2019-11-21 Gerbers unzipped for kitspace
2019-11-21 Adding kitspace.yaml
2019-11-22 Adding multy kitspace and 1 click BOMs
2019-11-22 first user manual draft, proofreading required!
2019-11-23 combinumerals font
2019-11-24 chapter 2 first read through
2019-11-24 R28 set to N.C.
2019-11-25 user manual firmware upgrade changed
2019-11-25 DCP405 Eagle files updated
2019-11-25 minor BOM changes
2019-11-26 chapters 3 and 4 read through & corrections
2019-11-30 Chapter 5 read through
2019-12-01 Accepted changes in user manual (1-5)
2019-12-02 a couple of very minor changes https://github.com/eez-open/modular-psu/pull/58#issuecomment-560120879 and https://github.com/eez-open/modular-psu/pull/55#issuecomment-560120683
2019-12-02 very few changes for chapter 6
2019-12-02 a couple of minor corrections
2019-12-02 a couple of minor changes
2019-12-02 very few changes for chapter 9
2019-12-04 user manual data logging chapter
2019-12-07 #53 (DCM220 r2B6)
2019-12-07 DCM220 r2B6 .ioc file
2019-12-07 DCM220 BOM update
2019-12-12 MCU r2B1 with Ethernet rotated
2019-12-13 MCU r2B1 with Ethernet and USB rotated
2019-12-14 DCP405 r2B8
2019-12-19 AUX PS PCB improvements, DCM220 ZD2, ZD4 correction
2019-12-20 DCP405 BOM corrections
2019-12-21 clean up Gerber files
2019-12-21 readme.md links
2019-12-21 unzip Gerbers for Kitspace
2019-12-22 DCP405 X2 BOM update
2019-12-23 Update 1-click-bom for dcm220
2020-01-04 DCP405, DCM220 new pictures
2020-01-04 DCM220 EEPROM mmoved, OSHWA UID added
2020-01-04 DCP405 EEPROM moved, OSHWA UID added
2020-01-05 DCP405 CC compensation correction, split BOMs
2020-01-06 DCP405 D17, ZD5 added
2020-01-07 move MCU kicad to previous designs
2020-01-11 #63, remove BOOT sw from AUX-PS
2020-01-13 DCP405 CC correction for DP
2020-01-13 add OSHWA ID on BP3C PCB
2020-01-13 DCP405 D17 set to N.C., DIB v1.0 update
2020-01-14 MCU PCB small correction
2020-01-14 new enclosure front and rear panel
2020-01-16 rear panel Ethernet holes correction
2020-01-21 MCU r2B4, battery holder moved to opposite side
2020-01-26 AUX-PS PCB layout update
2020-01-29 DCM220 OE pull-down added
2020-01-29 Centroid files added
2020-01-31 DCM220 HSE removed
2020-02-20 DCP405 OVP adjustment
2020-02-20 DCP405 centroid files update
2020-02-21 Updating BP3 1 click BOM
2020-02-21 Adding new DCM220 BOM
2020-02-21 Adding DCP405
2020-02-21 New BOM for MCU
2020-02-21 Removing dash - fix RS part
2020-02-21 shift by 1
2020-03-06 MCU BOM R28, R29 correction
2020-03-11 AUX-PS SW1 value fixed
2020-03-11 OSHW logo added
2020-03-20 MCU PCB inner layers extension name
2020-03-23 DCP405 swap LED1 and LED2 in BOM
2020-03-24 MCU SDcard PCB pads adjustment
2020-03-26 User manual draft v0.3
2020-03-29 User manual datetime settings update
2020-04-07 Small BOM fixes, first German user manual commit
2020-04-07 final proof of chapter 3
2020-04-07 user manual: channel trigger settings
2020-04-08 MCU part number updated in schematics
2020-04-08 final proof of ch4 system settings
2020-04-09 final proofread completed
2020-04-12 DCM220 BOM update (R45,R69)
2020-04-15 German user manual update
2020-04-17 minor changes to chapter 11
2020-04-17 ramp and delay editing
2020-04-17 User manual v1.0
2020-04-18 User manual links update
2020-04-18 User manual lower PDF resolution
2020-04-21 kit assembly instructions
2020-04-24 Suggested improvements to BB3 kit assembly instructions
2020-04-25 mcdanlj, dunkemhigh changes in kit assembly instructions
2020-04-26 update module pictures
2020-04-26 MCU readme.md update
2020-04-28 EEZ BB3 enclosure and bare PCBs assembly first commit
2020-04-28 Changing R45,R69 to 100K
2020-05-04 User manual firmware upgrade corrections
2020-05-05 DIB module templates
2020-05-09 calibration procedures - some small suggested improvements
2020-05-10 User manual v1.01
2020-05-22 BP3C description fixed
2020-05-26 DCP405 fuse rating changed
2020-06-02 MCU ZD1 value correction
2020-06-11 MCU .ioc version update
2020-06-12 DIB v1.1, BP3C r3B3
2020-06-12 wire harness doc
2020-06-12 BP3C new ZD1-ZD4 type
2020-06-12 DIB alternative IRQs added
2020-06-29 MCU readme update
2020-07-30 DCP405 and enclosure BOM update
2020-08-26 ULVO levels update for power modules
2020-08-26 web content folder
2020-08-26 web content PDF file
2020-08-28 FB values updated for DCP405 and DCM220
2020-09-09 MCU I2C pull-up update
2020-09-09 MCU IC6 model type update
2020-09-25 added cooling fan alternative
2020-11-01 liberapay badge
2020-11-01 liberapay badgefix
2020-11-06 combined LRS/EPP Mean Well support
2020-11-08 BP3C X5,X6,X7 package desc. update
2020-12-06 enclosure picture update
2020-12-25 enclosure bottom plate corrections
2020-12-25 enclosure front panel corrections
2020-12-25 enclosure bottom plate corrections (2)
2020-12-25 enclosure top plate corrections
2020-12-25 enclosure front panel corrections (3)
2020-12-25 enclosure display support corrections
2020-12-28 DIB v1.2 specification (ADIB added)
2021-01-31 MCU and DCP BOM small changes
2021-02-01 BP3C bottom layer cleanup
2021-02-12 User manual update
2021-02-15 New AUX-PS, #70, #83, #84
2021-02-15 New MCU, #70, #73, #75, #84, #85, #86, #90
2021-02-15 New DCP405, #81, #96
2021-02-16 Benutzerhandbuch v1.04 thanks to Jochen Hammer
2021-02-19 #97, User manual updates
2021-03-13 #103
2021-03-21 #105
2021-03-25 links fixed in README.md
2021-03-31 .ioc update, SPI speed adjustment
2021-04-01 User manual v1.05
2021-04-21 README.md updates
2021-06-27 PGND replaced with GND on few places
2021-09-23 New chapters in User manual
2021-09-23 Made relation of jumpers to PWM channel explicit.
2021-09-24 Add speaker alternative in BOM
2021-10-03 PCB layout for SMD/THT loudspeaker
2022-11-29 User manual 1.09
2023-02-16 Add readme paths in kitspace.yaml
2023-08-24 DCP405 r4 preliminary design
2023-08-24 DCP405 r4 EDA files
2023-08-24 4-layer cam file update
2023-08-25 Update Note 3.1. in DCP405 schematics
2024-01-02 AUX-PS module migration to KiCad
2024-01-03 BP3C and DIB module template migration to KiCad
2024-01-04 Eagle schematics pdf files
